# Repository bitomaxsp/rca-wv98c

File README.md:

# RCA WV98C

RCA WV98C schematic and PCB in KiCAD

See [here](https://www.radiomuseum.org/r/rca_senior_voltohmyst_wv_98c.html)

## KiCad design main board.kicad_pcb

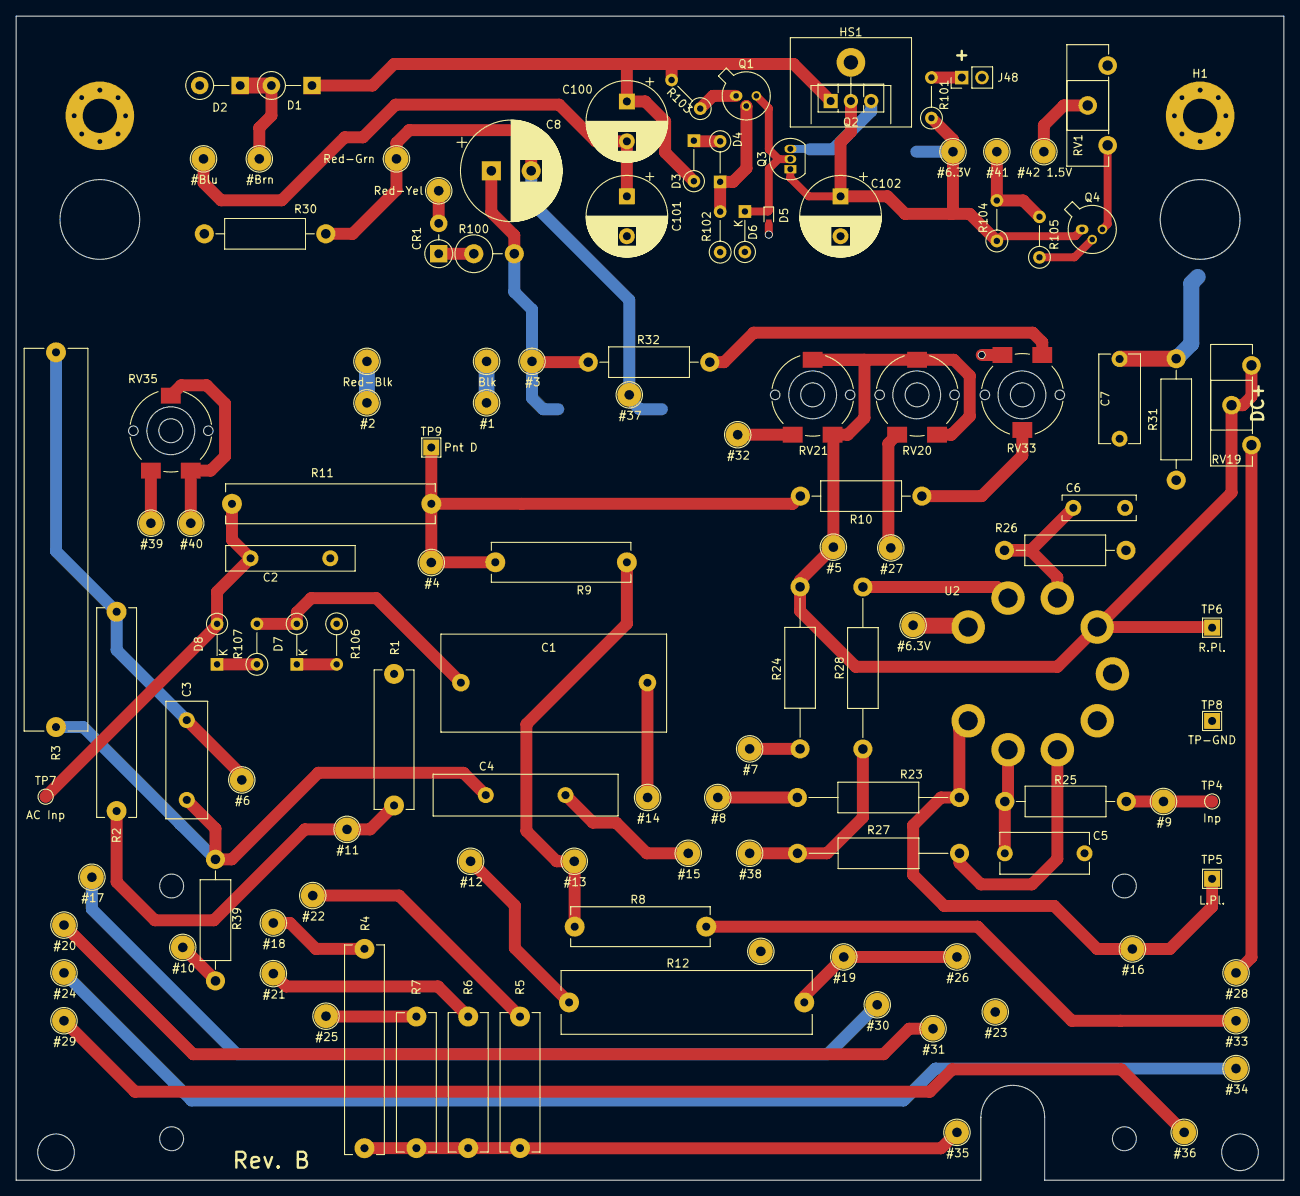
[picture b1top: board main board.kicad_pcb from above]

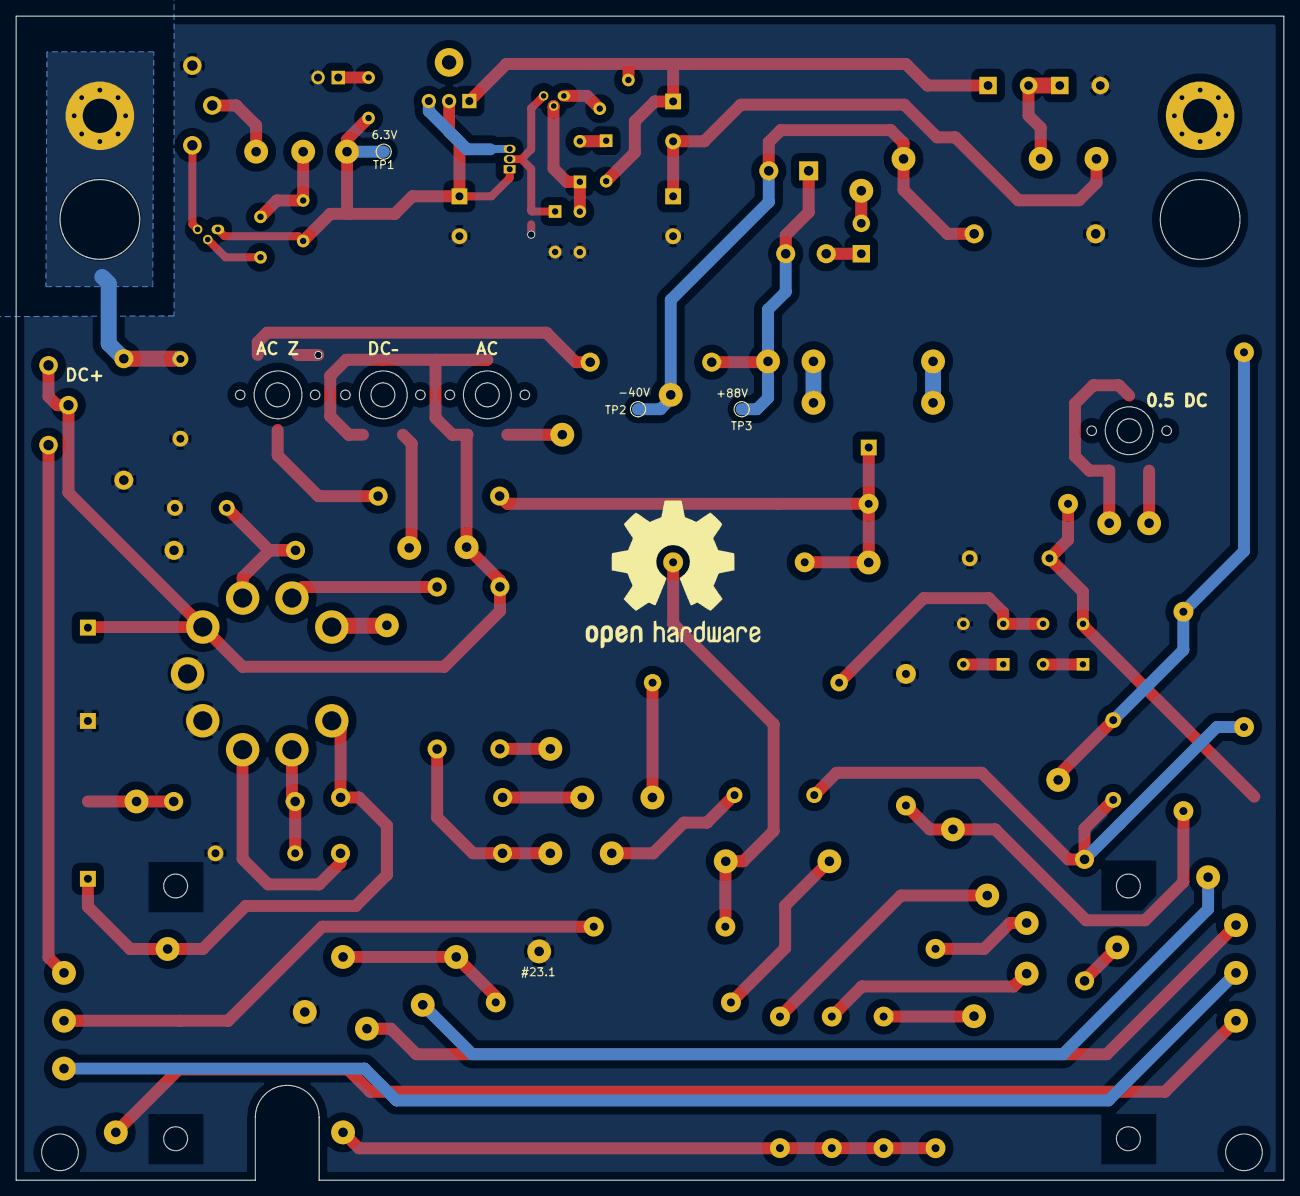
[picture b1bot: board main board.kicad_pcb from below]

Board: 2 copper layers, 158.9 x 145.9 mm, 124 parts (3 on the bottom side), 64 nets.

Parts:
C1: 0.05uF; 6PSS50
C2: 0.02uF; 562R5GAS20-C2
C3: 24pF; C_Disc_D14.5mm_W5.0mm_P10.00mm
C4: 0.1uF; 562R20GAP10-C4
C5, C7: 0.01uF; C_Disc_D11.0mm_W5.0mm_P10.00mm
C6: 0.005uF; S502M39Z5UN-C6
C8: 10uF; CP_Radial_D12.5mm_P5.00mm
C100, C101: 2000uF; CP_Radial_D10.0mm_P5.00mm
C102: 1000uF; CP_Radial_D10.0mm_P5.00mm
CR1: 4004; D_DO-41_SOD81_P3.81mm_Vertical_AnodeUp
D1, D2: 1N4001; D_DO-41_SOD81_P5.08mm_Vertical_KathodeUp
D3, D4, D7, D8: 1N4148; D_DO-35_SOD27_P5.08mm_Vertical_KathodeUp
D5: 6V9; D_SOD-523
D6: 6V9; D_DO-35_SOD27_P5.08mm_Vertical_KathodeUp
H1: Earth; MountingHole_4.3mm_M4_Pad_Via
HS1: Heatsink; heatsink
J1: #15; Hole_Din1.2mm_Dout3mm
J2: Red-Blk; Hole_Din1.2mm_Dout3mm
J3: #2; Hole_Din1.2mm_Dout3mm
J4: Blk; Hole_Din1.2mm_Dout3mm
J5: #1; Hole_Din1.2mm_Dout3mm
J6: #6; Hole_Din1.2mm_Dout3mm
J7: #10; Hole_Din1.2mm_Dout3mm
J8: Red-Yel; Hole_Din1.2mm_Dout3mm
J9: Red-Grn; Hole_Din1.2mm_Dout3mm
J10: #11; Hole_Din1.2mm_Dout3mm
J11: #14; Hole_Din1.2mm_Dout3mm
J12: #37; Hole_Din1.2mm_Dout3mm
J13: #3; Hole_Din1.2mm_Dout3mm
J14: #23; Hole_Din1.2mm_Dout3mm
J15: #33; Hole_Din1.2mm_Dout3mm
J16: #38; Hole_Din1.2mm_Dout3mm
J17: #4; Hole_Din1.2mm_Dout3mm
J18: #13; Hole_Din1.2mm_Dout3mm
J19: #9; Hole_Din1.2mm_Dout3mm
J20: #18; Hole_Din1.2mm_Dout3mm
J21: #22; Hole_Din1.2mm_Dout3mm
J22: #21; Hole_Din1.2mm_Dout3mm
J23: #25; Hole_Din1.2mm_Dout3mm
J24: #8; Hole_Din1.2mm_Dout3mm
J25: #16; Hole_Din1.2mm_Dout3mm
J26: #12; Hole_Din1.2mm_Dout3mm
J27: #35; Hole_Din1.2mm_Dout3mm
J28: #7; Hole_Din1.2mm_Dout3mm
J29: #19; Hole_Din1.2mm_Dout3mm
J30: #26; Hole_Din1.2mm_Dout3mm
J31: #5; Hole_Din1.2mm_Dout3mm
J32: #28; Hole_Din1.2mm_Dout3mm
J33: #32; Hole_Din1.2mm_Dout3mm
J34: #39; Hole_Din1.2mm_Dout3mm
J35: #27; Hole_Din1.2mm_Dout3mm
J36: #40; Hole_Din1.2mm_Dout3mm
J37: #17; Hole_Din1.2mm_Dout3mm
J38: #20; Hole_Din1.2mm_Dout3mm
J39: #24; Hole_Din1.2mm_Dout3mm
J40: #29; Hole_Din1.2mm_Dout3mm
J41: #30; Hole_Din1.2mm_Dout3mm
J42: #31; Hole_Din1.2mm_Dout3mm
J43: #34; Hole_Din1.2mm_Dout3mm
J44: #36; Hole_Din1.2mm_Dout3mm
J45: #Brn; Hole_Din1.2mm_Dout3mm
J46: #Blu; Hole_Din1.2mm_Dout3mm
J47: #41; Hole_Din1.2mm_Dout3mm
J48: LED conn; PinHeader_1x02_P2.54mm_Vertical
J49: #42 1.5V; Hole_Din1.2mm_Dout3mm
J50, J51: #6.3V; Hole_Din1.2mm_Dout3mm
J52: #23.1; Hole_Din1.2mm_Dout3mm
Q1, Q4: 2N2907; TO-18-3
Q2: BD136; TO-126-3_Vertical
Q3: PN2222A; TO-92_Inline
R1: 150k; R1-like
R2: 324k; R2
R3: 900k; R3
R4: 9.75; R2
R5: 100; R1-like
R6: 1k; R1-like
R7: 10k; R1-like
R8: 2.12M; R1-like
R9: 8.49M; R1-like
R10: 91M; R_Axial_DIN0411_L9.9mm_D3.6mm_P15.24mm_Horizontal
R11: 16M; R2
R12: 7M; R12
R23, R24: 10k; R_Axial_DIN0411_L9.9mm_D3.6mm_P20.32mm_Horizontal
R25: 3.3M; R_Axial_DIN0411_L9.9mm_D3.6mm_P15.24mm_Horizontal
R26: 6.8M; R_Axial_DIN0411_L9.9mm_D3.6mm_P15.24mm_Horizontal
R27, R28: 330; R_Axial_DIN0411_L9.9mm_D3.6mm_P20.32mm_Horizontal
R30: 27k; R_Axial_DIN0411_L9.9mm_D3.6mm_P15.24mm_Horizontal
R31: 1M; R_Axial_DIN0411_L9.9mm_D3.6mm_P15.24mm_Horizontal
R32: 47k; R_Axial_DIN0411_L9.9mm_D3.6mm_P15.24mm_Horizontal
R39: 1k; R_Axial_DIN0411_L9.9mm_D3.6mm_P15.24mm_Horizontal
R100: 1k; R_Axial_DIN0414_L11.9mm_D4.5mm_P5.08mm_Vertical
R101: 330; R_Axial_DIN0207_L6.3mm_D2.5mm_P5.08mm_Vertical
R102: 20k; R_Axial_DIN0207_L6.3mm_D2.5mm_P5.08mm_Vertical
R103: 33; R_Axial_DIN0207_L6.3mm_D2.5mm_P5.08mm_Vertical
R104: 10k; R_Axial_DIN0207_L6.3mm_D2.5mm_P5.08mm_Vertical
R105: 1k; R_Axial_DIN0207_L6.3mm_D2.5mm_P5.08mm_Vertical
R106, R107: 180; R_Axial_DIN0207_L6.3mm_D2.5mm_P5.08mm_Vertical
RV1, RV19: 10k; Potentiometer_Piher_PT-15-H01_Horizontal
RV20, RV21, RV33, RV35: 10k; Potentiometer_Piher_PS_PSX-10-V60_Vertical
TP1: 6.3V; TestPoint_Pad_D1.5mm
TP2: -40V; TestPoint_Pad_D1.5mm
TP3: +88V; TestPoint_Pad_D1.5mm
TP4: Inp; TestPoint_Pad_D1.5mm
TP5: L.Pl.; TestPoint_THTPad_2.0x2.0mm_Drill1.0mm
TP6: R.Pl.; TestPoint_THTPad_2.0x2.0mm_Drill1.0mm
TP7: AC Inp; TestPoint_Pad_D1.5mm
TP8: TP-GND; TestPoint_THTPad_2.0x2.0mm_Drill1.0mm
TP9: Pnt D; TestPoint_THTPad_2.0x2.0mm_Drill1.0mm
U2: ECC83; 12AU7A

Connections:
Earth: C7.1, H1.1, R31.2
GND: C2.2, C5.1, C6.2, C7.2, C101.2, C102.2, D2.2, D5.2, D6.2, J14.1, J48.2, J52.1, R1.2, R26.1, R30.1, R31.1, R102.1, R106.1, RV1.3, RV33.3, TP8.1, U2.4, U2.5
unnamed: C1.1, J11.1
unnamed: C1.2, D7.2, R107.2
unnamed: C2.1, D8.2, R11.2, TP7.1
unnamed: C3.1, J6.1, R2.1, R3.1
unnamed: C3.2, C4.1, R3.2, R39.2
unnamed: C4.2, J1.1
unnamed: C5.2, R25.1, U2.2
unnamed: C6.1, R26.2, U2.7
unnamed: C8.1, J13.1, R32.2, R100.2, TP3.1
unnamed: C8.2, J9.1, J12.1, R30.2, TP2.1
unnamed: C100.1, D1.1, D3.2, Q2.1, R103.2
unnamed: C100.2, C101.1, J46.1
unnamed: C102.1, J50.1, Q2.2, Q3.1, Q4.1, R101.1, R104.1, TP1.1
unnamed: CR1.1, R100.1
unnamed: CR1.2, J8.1
unnamed: D1.2, D2.1, J45.1
unnamed: D3.1, D4.2
unnamed: D4.1, Q1.2, R102.2
unnamed: D5.1, D6.1, Q1.3, Q3.2
unnamed: D7.1, R106.2
unnamed: D8.1, R107.1
unnamed: J2.1, J3.1
unnamed: J4.1, J5.1
unnamed: J7.1, R39.1
unnamed: J10.1, R1.1, R2.2
unnamed: J15.1, R8.1
unnamed: J16.1, R27.1, R28.1
unnamed: J17.1, R9.2, R10.2, R11.1, TP9.1
unnamed: J18.1, R8.2, R9.1
unnamed: J19.1, R25.2, TP4.1
unnamed: J20.1, R4.1
unnamed: J21.1, R5.1
unnamed: J22.1, R6.1
unnamed: J23.1, R7.1
unnamed: J24.1, R23.2
unnamed: J25.1, R23.1, TP5.1, U2.1
unnamed: J26.1, R12.1
unnamed: J27.1, R4.2, R5.2, R6.2, R7.2
unnamed: J28.1, R24.2
unnamed: J29.1, J30.1, R12.2
unnamed: J31.1, R24.1, RV19.2, RV19.3, RV20.2, RV20.3, RV21.2, RV21.3, TP6.1, U2.6
unnamed: J32.1, RV19.1
unnamed: J33.1, RV21.1
unnamed: J34.1, RV35.1
unnamed: J35.1, RV20.1
unnamed: J36.1, RV35.2, RV35.3
unnamed: J37.1, J41.1
unnamed: J38.1, J42.1
unnamed: J39.1, J43.1
unnamed: J40.1, J44.1
unnamed: J47.1, R104.2, R105.2
unnamed: J48.1, R101.2
unnamed: J49.1, RV1.2
unnamed: J51.1, U2.9
unnamed: Q1.1, R103.1
unnamed: Q2.3, Q3.3
unnamed: Q4.2, R105.1
unnamed: Q4.3, RV1.1
unnamed: R10.1, RV33.2
unnamed: R27.2, U2.3
unnamed: R28.2, U2.8
unnamed: R32.1, RV33.1

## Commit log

2020-06-11 Initial main board revision. No footprints
2020-06-11 Docs
2020-06-12 Assign footprints which close to original
    Caps are assigned as close as possible
2020-06-12 Align all holes as close to original as possible
2020-06-13 Add big 4 node resistor and layout close to original
2020-06-13 Update doc with release link
2020-06-14 2 side layout with bottom gound plane
2020-06-14 Add heatsink for main BJT
2020-06-14 Use PNP as a switch
2020-06-15 Rotate main BJT correctly
2020-06-15 Add missing values after check
2020-06-15 Add earth grounding as in original
2020-06-15 Add correct release link
2020-06-21 Improve layout
2020-07-11 Fixes after Rev.A was assembled
2020-07-11 Add D point and remove J references from wire points
2020-07-13 Put back original resistors
2020-07-26 Remove 6AL5 and replace it with diodes
